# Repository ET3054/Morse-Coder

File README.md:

# Morse-Coder

Kurs:                   ET3054 Entwurf und Fertigung von Flachbaugruppen

Jahrgang:               2024

Gruppe:                 8

Teilnehmer:             Hendrik Stadler, Jasper Martin Kyeck, Sebastian Gust

Projekt:                Morse-Coder

Beschreibung:           Eingabe von Morse-Code mit auditivem Feedback und Übersetzung auf LCD-Display, Eingabe von Buchstaben/Wörtern über Dreh-Encoder (Joystick) und Übersetzung als auditiven Sound in Morse-Code
                        mögliche Erweiterung -> Training und Übungen für Encoding und Decoding von Morse-Code

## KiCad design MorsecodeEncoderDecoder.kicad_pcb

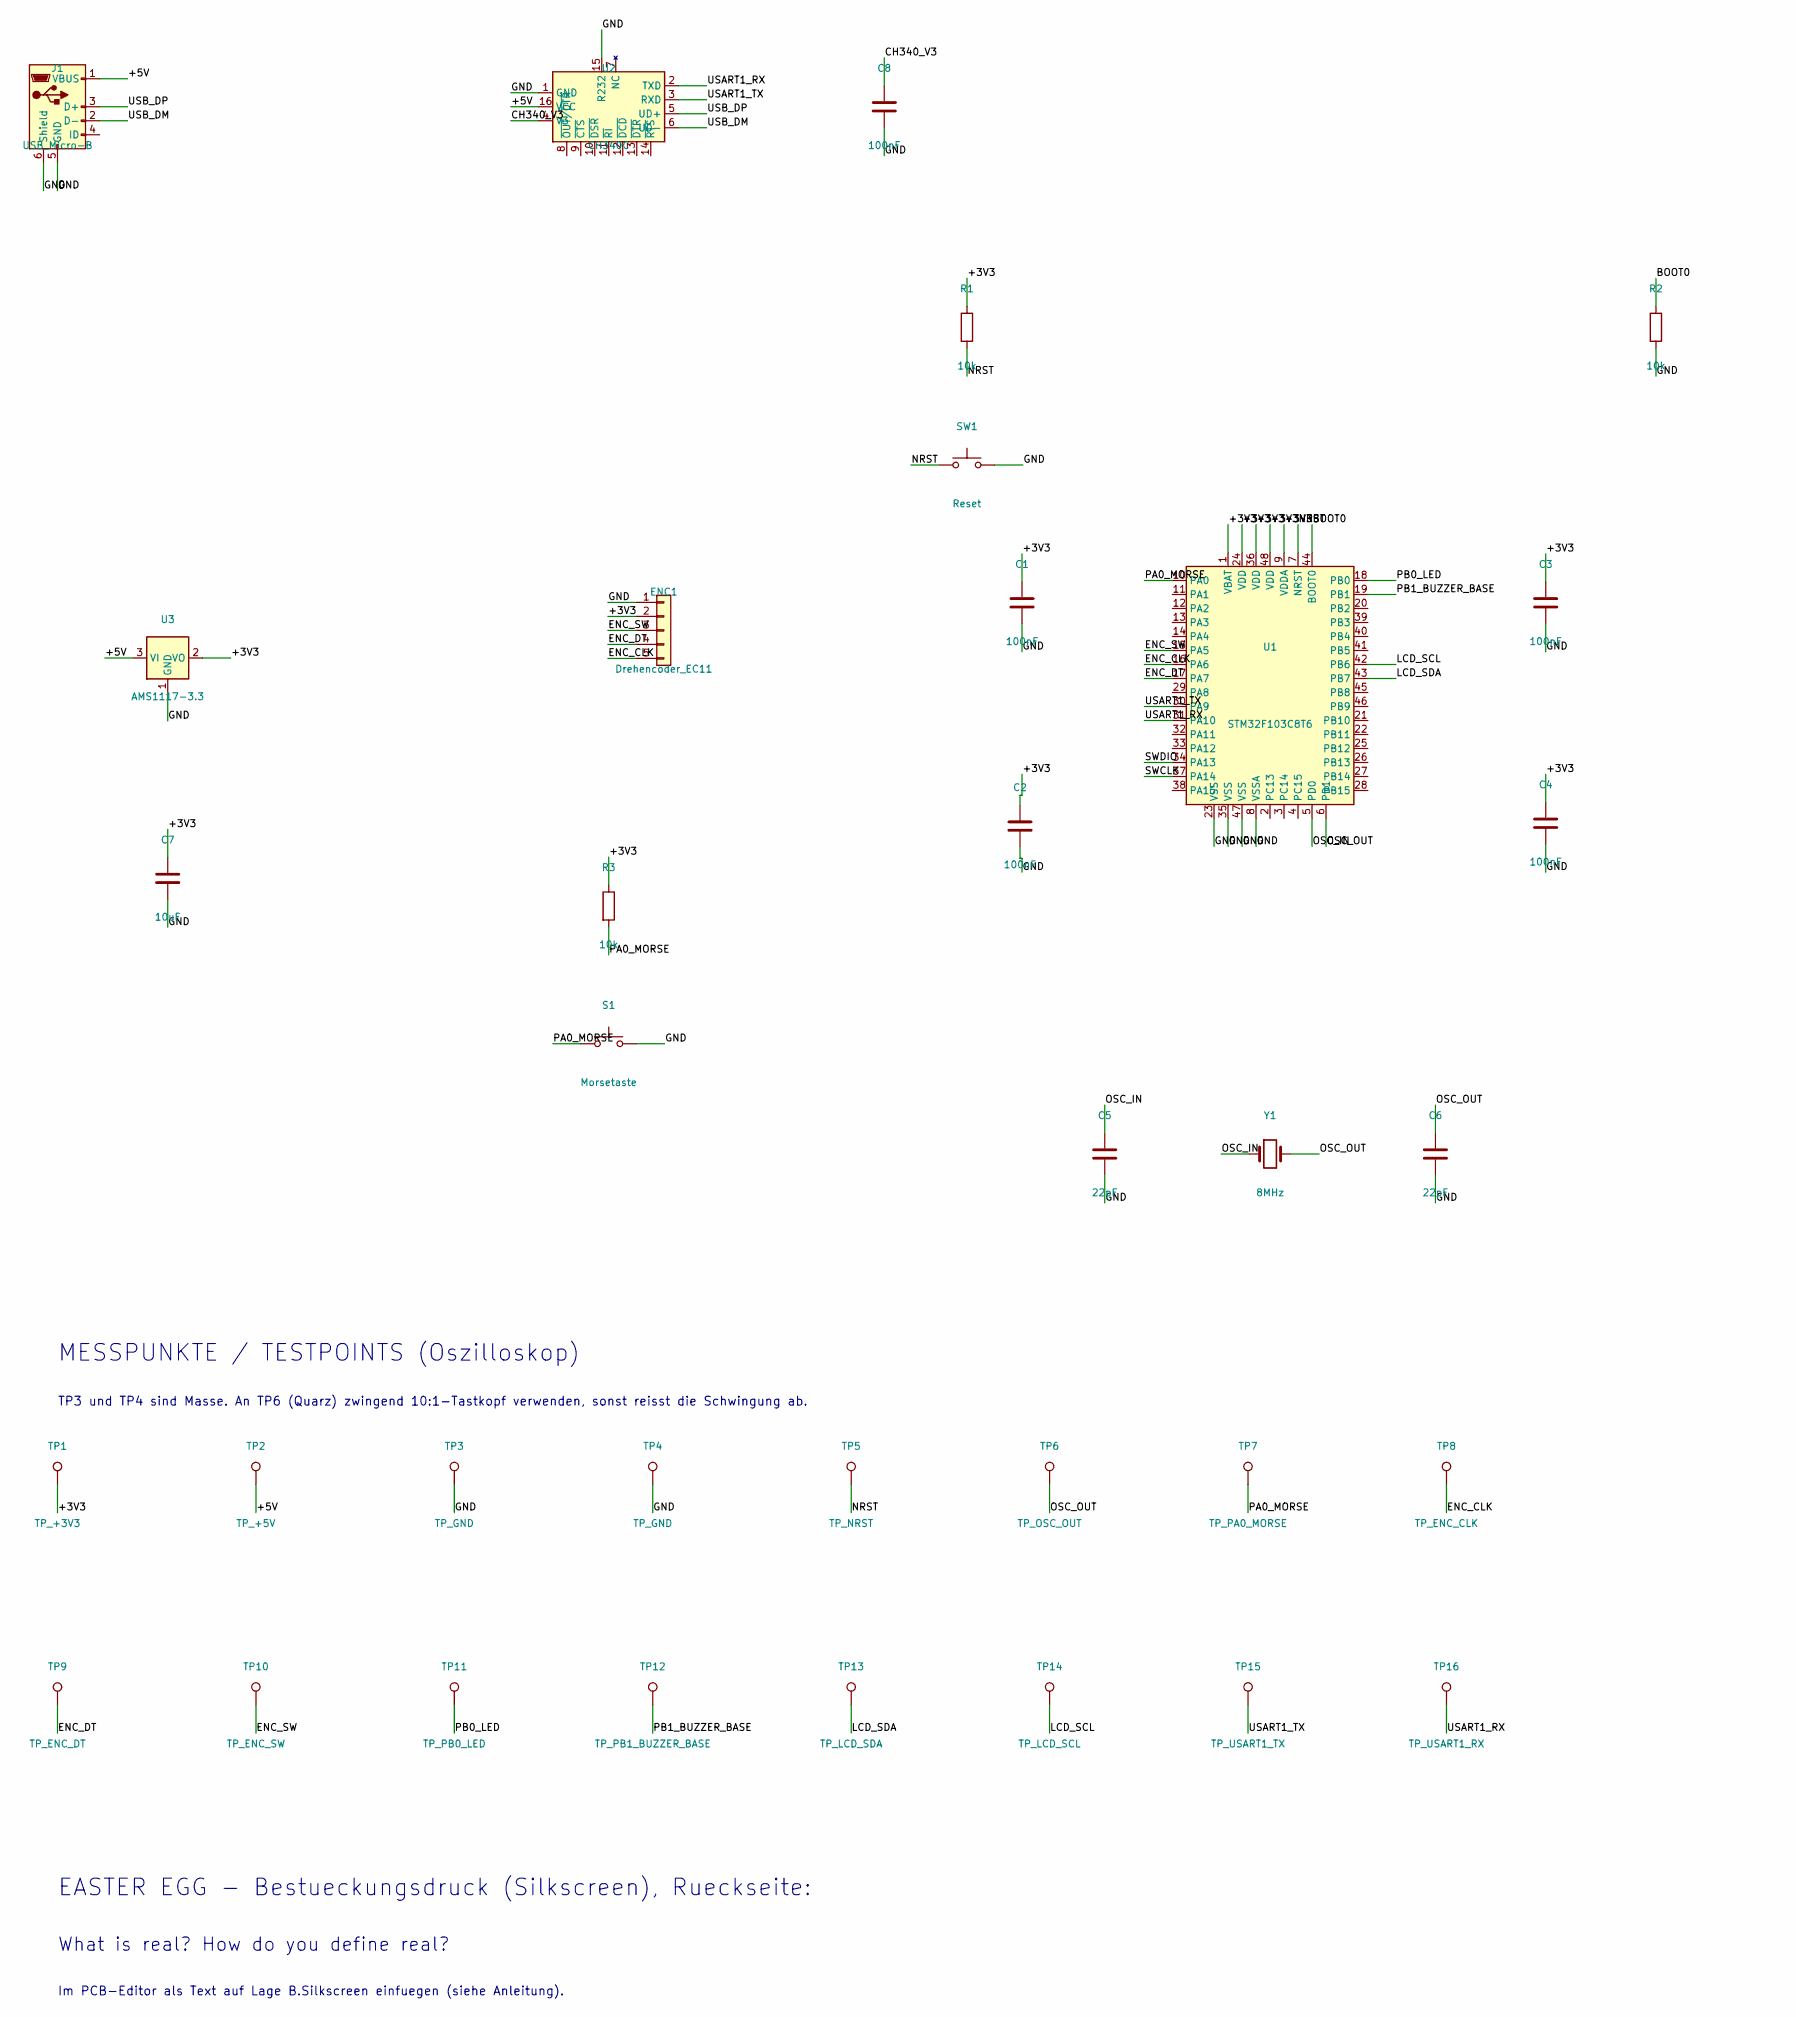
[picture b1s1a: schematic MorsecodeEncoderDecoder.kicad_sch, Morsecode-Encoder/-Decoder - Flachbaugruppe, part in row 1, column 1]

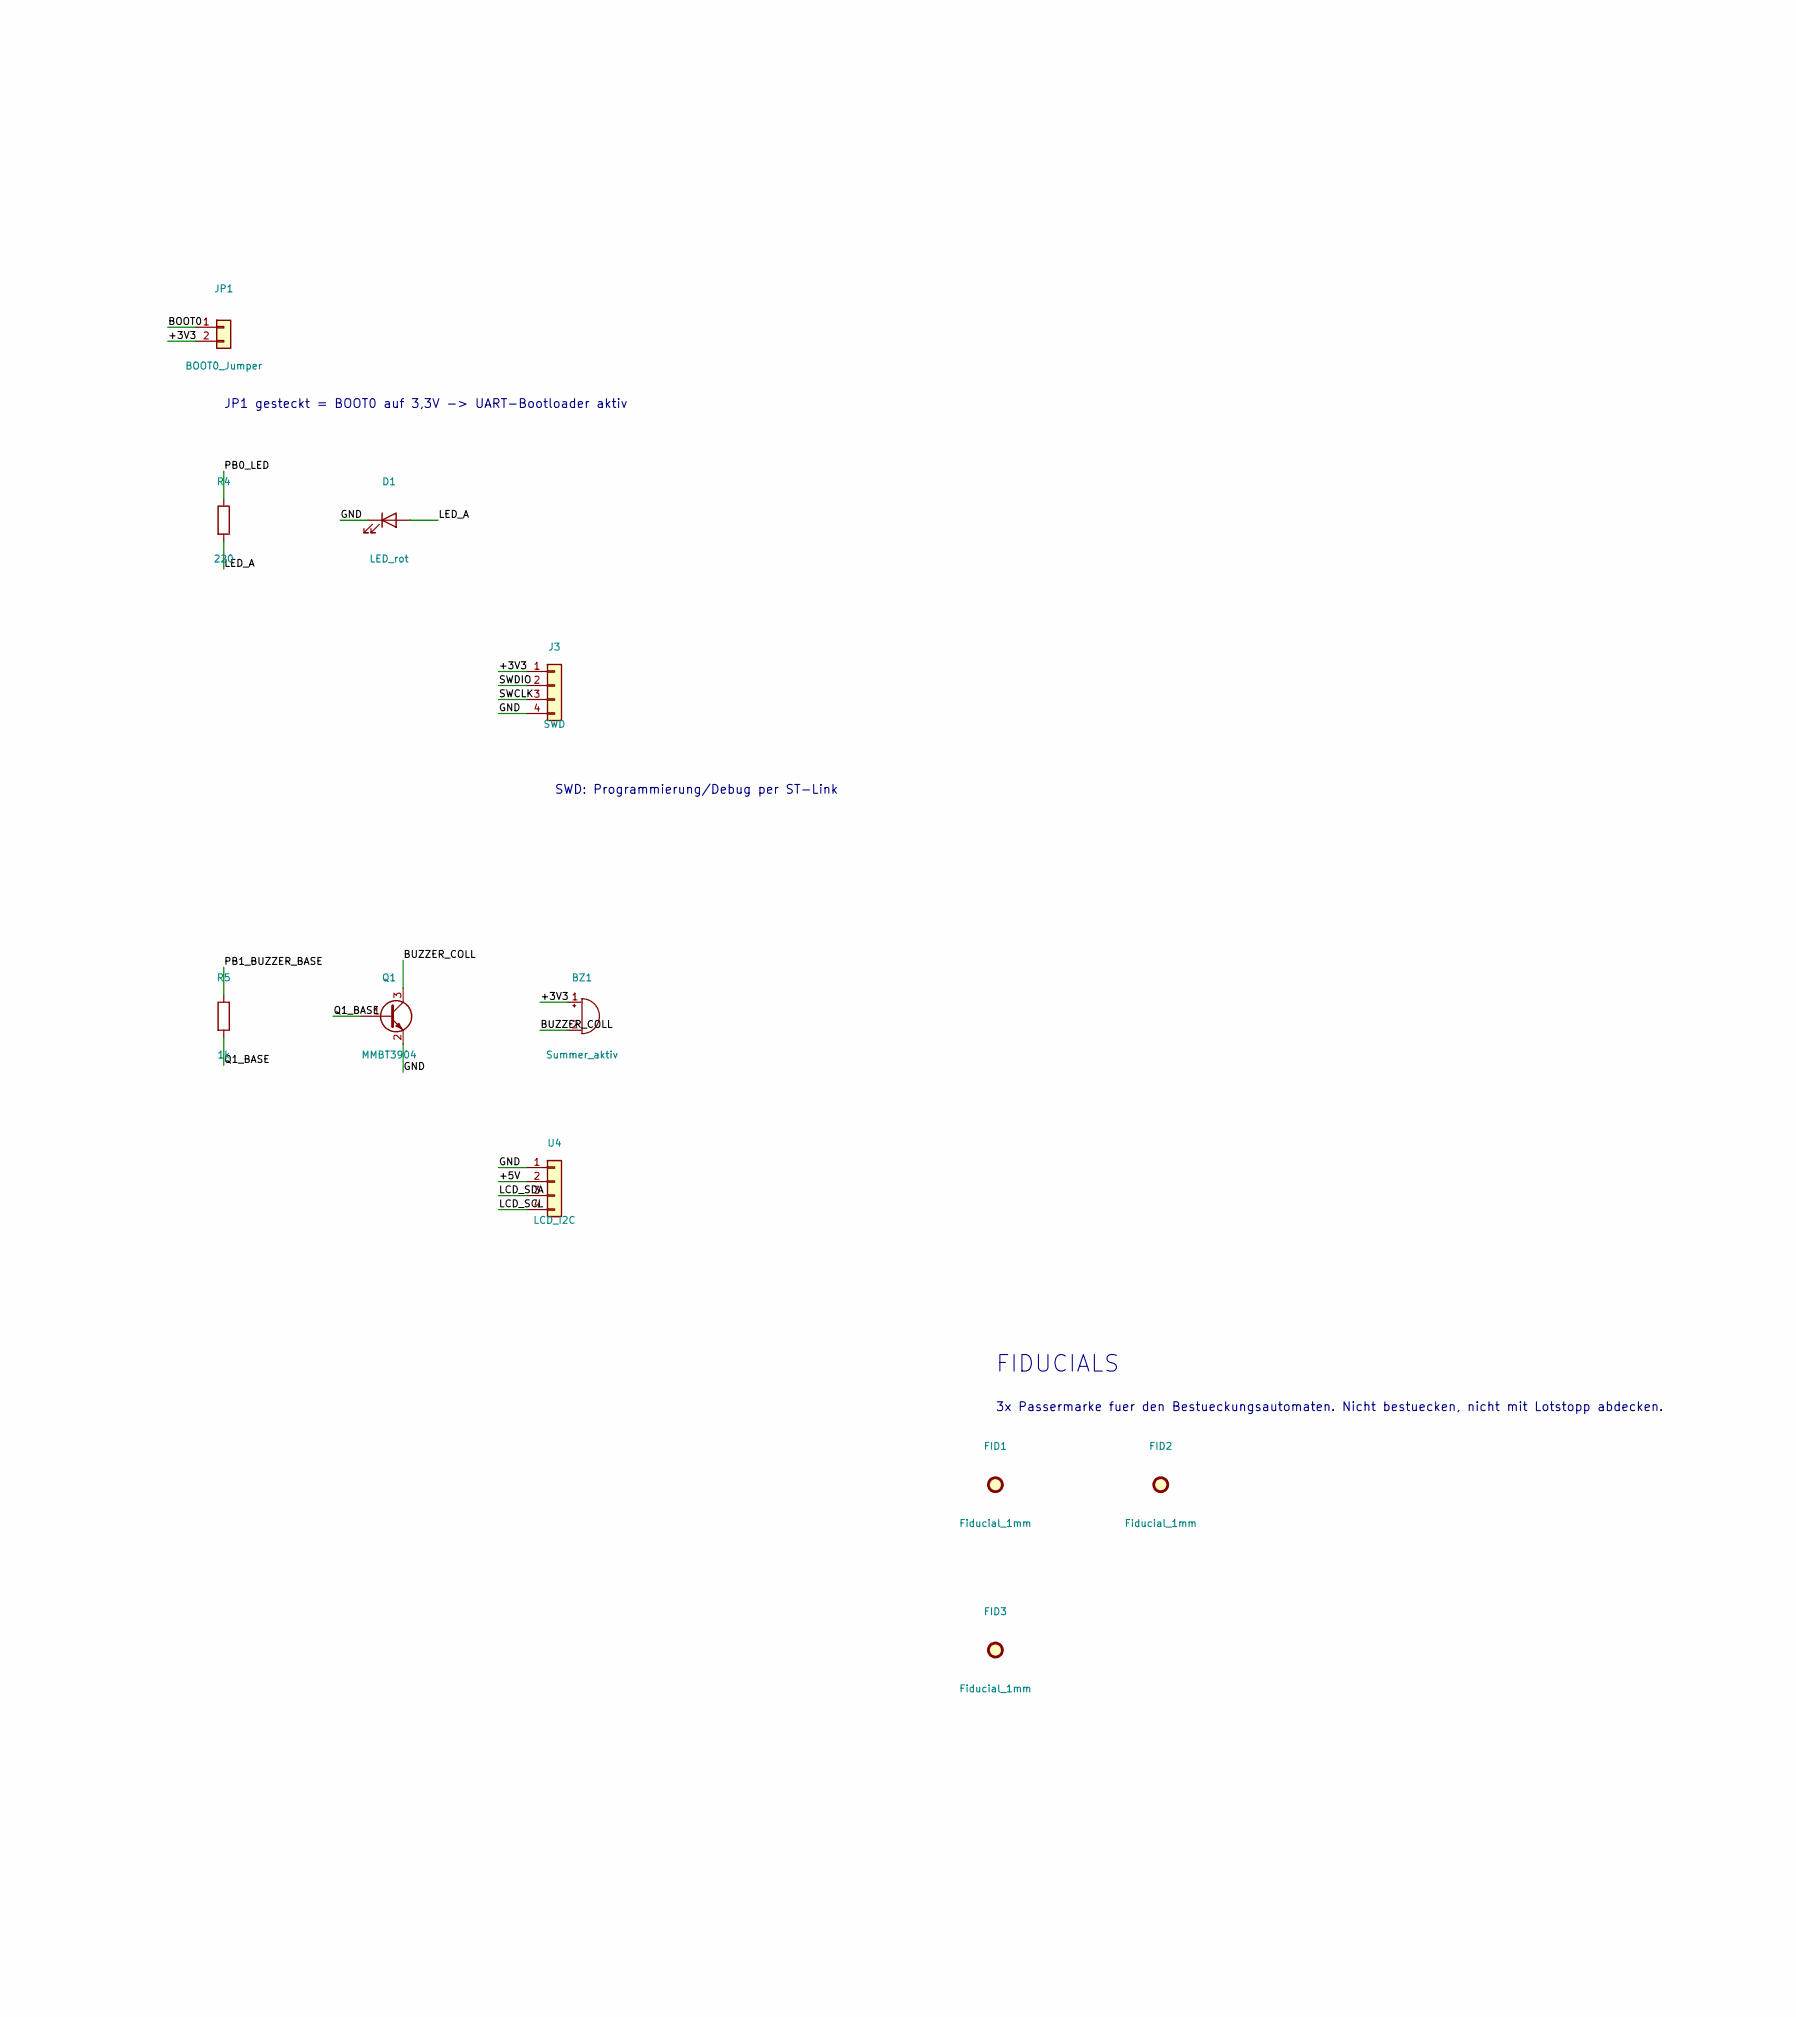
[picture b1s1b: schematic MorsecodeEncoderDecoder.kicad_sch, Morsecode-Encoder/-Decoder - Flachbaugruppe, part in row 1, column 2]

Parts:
BZ1: Summer_aktiv; Buzzer_12x9.5RM7.6; LCSC PRUEFEN
C1, C2, C3, C4, C8: 100nF; C_0805_2012Metric; LCSC C49678
C5, C6: 22pF; C_0805_2012Metric; LCSC PRUEFEN
C7: 10uF; C_0805_2012Metric; LCSC C15850
D1: LED_rot; LED_0805_2012Metric; LCSC PRUEFEN
ENC1: Drehencoder_EC11; PinHeader_1x05_P2.54mm_Vertical; LCSC PRUEFEN
FID1, FID2, FID3: Fiducial_1mm; Fiducial_1mm_Mask2mm
J1: USB_Micro-B; USB_Micro-B_Molex-105017-0001; LCSC PRUEFEN
J3: SWD; PinHeader_1x04_P2.54mm_Vertical; LCSC PRUEFEN
JP1: BOOT0_Jumper; PinHeader_1x02_P2.54mm_Vertical; LCSC PRUEFEN
Q1: MMBT3904; SOT-23; LCSC PRUEFEN
R1, R2, R3: 10k; R_0805_2012Metric; LCSC C17414
R4: 220; R_0805_2012Metric; LCSC PRUEFEN
R5: 1k; R_0805_2012Metric; LCSC PRUEFEN
S1: Morsetaste; SW_SPST_TL3342; LCSC PRUEFEN
SW1: Reset; SW_SPST_TL3342; LCSC PRUEFEN
TP1: TP_+3V3; TestPoint_Pad_D1.5mm
TP2: TP_+5V; TestPoint_Pad_D1.5mm
TP3, TP4: TP_GND; TestPoint_Pad_D1.5mm
TP5: TP_NRST; TestPoint_Pad_D1.5mm
TP6: TP_OSC_OUT; TestPoint_Pad_D1.5mm
TP7: TP_PA0_MORSE; TestPoint_Pad_D1.5mm
TP8: TP_ENC_CLK; TestPoint_Pad_D1.5mm
TP9: TP_ENC_DT; TestPoint_Pad_D1.5mm
TP10: TP_ENC_SW; TestPoint_Pad_D1.5mm
TP11: TP_PB0_LED; TestPoint_Pad_D1.5mm
TP12: TP_PB1_BUZZER_BASE; TestPoint_Pad_D1.5mm
TP13: TP_LCD_SDA; TestPoint_Pad_D1.5mm
TP14: TP_LCD_SCL; TestPoint_Pad_D1.5mm
TP15: TP_USART1_TX; TestPoint_Pad_D1.5mm
TP16: TP_USART1_RX; TestPoint_Pad_D1.5mm
U1: STM32F103C8T6; LQFP-48_7x7mm_P0.5mm; LCSC C8734
U2: CH340C; SOIC-16_3.9x9.9mm_P1.27mm; LCSC C84681
U3: AMS1117-3.3; SOT-223-3_TabPin2; LCSC C6186
U4: LCD_I2C; PinHeader_1x04_P2.54mm_Vertical; LCSC PRUEFEN
Y1: 8MHz; Crystal_SMD_3225-4Pin_3.2x2.5mm; LCSC PRUEFEN

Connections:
/+3V3: BZ1.1 (+), C1.1, C2.1, C3.1, C4.1, C7.1, ENC1.2, J3.1, JP1.2, R1.1, R3.1, TP1.1 (1_1), U1.1 (VBAT), U1.9 (VDDA), U1.24 (VDD), U1.36 (VDD), U1.48 (VDD), U3.2 (VO)
/+5V: J1.1 (VBUS), TP2.1 (1_1), U2.16 (VCC), U3.3 (VI), U4.2
/BOOT0: JP1.1, R2.1, U1.44 (BOOT0)
/BUZZER_COLL: BZ1.2 (-), Q1.3 (C)
/CH340_V3: C8.1, U2.4 (V3)
/ENC_CLK: ENC1.5, TP8.1 (1_1), U1.16 (PA6)
/ENC_DT: ENC1.4, TP9.1 (1_1), U1.17 (PA7)
/ENC_SW: ENC1.3, TP10.1 (1_1), U1.15 (PA5)
/GND: C1.2, C2.2, C3.2, C4.2, C5.2, C6.2, C7.2, C8.2, D1.1 (K), ENC1.1, J1.5 (GND), J1.6 (Shield), J3.4, Q1.2 (E), R2.2, S1.2, SW1.2, TP3.1 (1_1), TP4.1 (1_1), U1.8 (VSSA), U1.23 (VSS), U1.35 (VSS), U1.47 (VSS), U2.1 (GND), U2.15 (R232), U3.1 (GND), U4.1
/LCD_SCL: TP14.1 (1_1), U1.42 (PB6), U4.4
/LCD_SDA: TP13.1 (1_1), U1.43 (PB7), U4.3
/LED_A: D1.2 (A), R4.2
/NRST: R1.2, SW1.1, TP5.1 (1_1), U1.7 (NRST)
/OSC_IN: C5.1, U1.5 (PD0), Y1.1
/OSC_OUT: C6.1, TP6.1 (1_1), U1.6 (PD1), Y1.2
/PA0_MORSE: R3.2, S1.1, TP7.1 (1_1), U1.10 (PA0)
/PB0_LED: R4.1, TP11.1 (1_1), U1.18 (PB0)
/PB1_BUZZER_BASE: R5.1, TP12.1 (1_1), U1.19 (PB1)
/Q1_BASE: Q1.1 (B), R5.2
/SWCLK: J3.3, U1.37 (PA14)
/SWDIO: J3.2, U1.34 (PA13)
/USART1_RX: TP16.1 (1_1), U1.31 (PA10), U2.2 (TXD)
/USART1_TX: TP15.1 (1_1), U1.30 (PA9), U2.3 (RXD)
/USB_DM: J1.2 (D-), U2.6 (UD-)
/USB_DP: J1.3 (D+), U2.5 (UD+)

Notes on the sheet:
What is real? How do you define real?
MESSPUNKTE / TESTPOINTS (Oszilloskop)
3x Passermarke fuer den Bestueckungsautomaten. Nicht bestuecken, nicht mit Lotstopp abdecken.
SWD: Programmierung/Debug per ST-Link
EASTER EGG - Bestueckungsdruck (Silkscreen), Rueckseite:
JP1 gesteckt = BOOT0 auf 3,3V -> UART-Bootloader aktiv
TP3 und TP4 sind Masse. An TP6 (Quarz) zwingend 10:1-Tastkopf verwenden, sonst reisst die Schwingung ab.
Im PCB-Editor als Text auf Lage B.Silkscreen einfuegen (siehe Anleitung).
FIDUCIALS

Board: 2 copper layers, 46 parts (0 on the bottom side), 25 nets, no tracks yet.
